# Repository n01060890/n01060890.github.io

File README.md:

# Smart Hive

Our project allows beekeepers to monitor multiple geographically distant hives via smartphones and tablets.

Externally, the Smart Hive documents changes in the hive's weight, and counts incoming and outgoing bees.
Internally, it captures multiple temperature and humidity data, in order to locate the bee cluster over the winter.

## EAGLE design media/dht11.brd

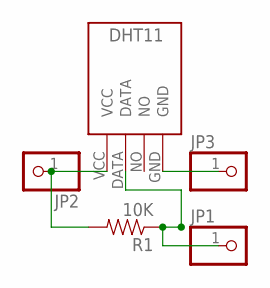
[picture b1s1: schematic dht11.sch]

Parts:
JP1, JP2, JP3: PINHD-1X1; 1X01
R1: 10K; AXIAL-0.3
U$1: DHT11

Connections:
unnamed: JP3.1, U$1.GND
unnamed: JP2.1, R1.P$2 (2), U$1.VCC
unnamed: JP1.1, R1.P$1 (1), U$1.DATA

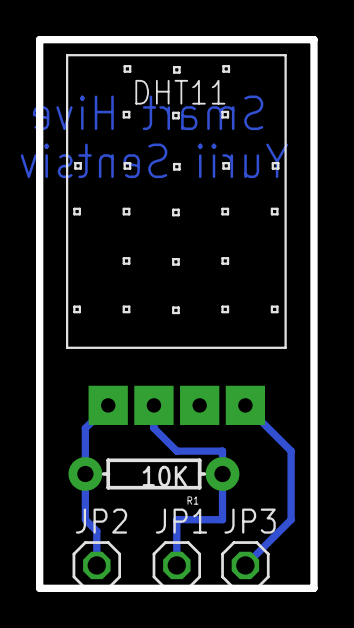
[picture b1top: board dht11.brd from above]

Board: 2 copper layers, 15.2 x 30.5 mm, 5 parts (0 on the bottom side), 3 nets.

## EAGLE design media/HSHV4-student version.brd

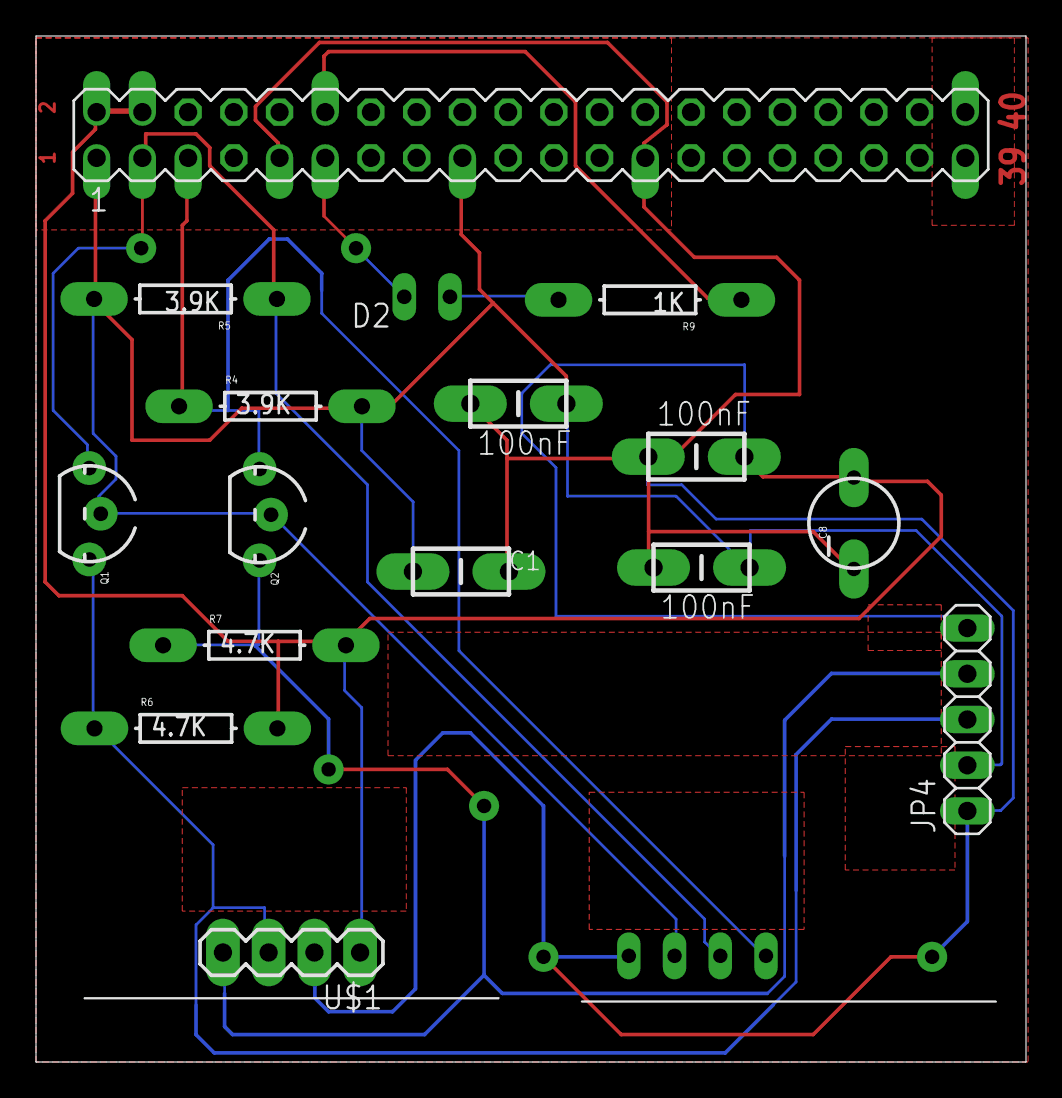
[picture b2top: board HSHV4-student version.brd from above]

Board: 2 copper layers, 55.0 x 57.0 mm, 17 parts (0 on the bottom side), 10 nets.

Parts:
C1, C2, C4, C5: 100nF; CAP-PTH-SMALL-KIT
C8: 10uF; CPOL-RADIAL-10UF-25V
D2: LED3MM-NS
IC1: DS3231; 8PTH
JP4: 1X05
K1: PIN20X2; PIN_20X2
Q1, Q2: MOSFET-NCHANNEL2N7000; TO-92
R4, R5: 3.9K; AXIAL-0.3
R6, R7: 4.7K; AXIAL-0.3
R9: 1K; AXIAL-0.3
U$1: PCF8591; 1X04

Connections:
+3V3: C1.1, C2.1, C4.2, IC1.2, JP4.2, K1.1, K1.17, Q1.2, Q2.2, R4.P$2, R5.P$2
+5V: C5.2, C8.1, JP4.5, K1.2, K1.4, R6.P$2, R7.P$2, U$1.1
GND: C1.2, C2.2, C4.1, C5.1, C8.2, IC1.1, JP4.1, K1.9, K1.25, U$1.2
GPIO17: D2.K, K1.11
GPIO18: K1.12, R9.P$1
unnamed: D2.A, R9.P$2
SCL1-3: IC1.4, K1.5, Q2.1, R4.P$1
SCL1-5: JP4.4, Q2.3, R7.P$1, U$1.4
SDA1-3: IC1.3, K1.3, Q1.1, R5.P$1
SDA1-5: JP4.3, Q1.3, R6.P$1, U$1.3

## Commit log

2016-09-20 Set up
2016-09-20 Updating content
2016-09-20 Picture resize
2016-09-20 Picture fix
2016-09-20 image resizing
2016-10-04 Updating web page
    Updating the progress
2016-10-04 Menu update
    Updating the navigation
2016-10-11 Week 6 update
2016-10-11 Week 6
    picture update
2016-10-11 Week 6
    Update
2016-10-25 Week 7
    Added week 7 content
2016-10-25 Week 8
    Added week 8 content
2016-10-25 Week 8(resubmission)
    Content is not visible
2016-10-25 Week 8(update)
    Placard link added
2016-10-25 Week 8(update)
    content not showing
2016-11-01 Week 9
    Adding content
2016-11-01 Week 9(added)
    Content not showing. Resubmission
2016-11-08 Week 10
    Progress report
2016-11-08 Week 10
    Content invisible
2016-11-15 Update directory
    Managing files folders
2016-11-15 Adding code
    Current code that I've used to get readings and display them into graph.
2016-11-15 Week 11
    Updating report
2016-11-22 Week 12
    Added progress perort on Week 12
2016-11-22 Week 12(content fix)
    Content is not appearing on web page.
2016-11-22 Week 12(fix)
2016-11-29 Week 13
    Presentation
2016-11-29 week 13
    adding media
2016-11-29 week 13
    fix
2016-12-06 Week 14
    Adding content
2016-12-06 Week 14
    Content fix
2016-12-06 Build Log
    Added Build Log page
2016-12-06 Build Log (fix)
2016-12-06 Build Log(Fix)
    Fixing html code, by replacing the C tags
2016-12-06 Build Log(fix 3)
    Updated buildlog page
2016-12-06 Build Log(fix 5)
    main page link
2016-12-11 Build Log(fix 6)
    added link to Build log in desription
2016-12-11 Build Log(Full update)
    Full update, with all files
2016-12-11 Build Log(Link fix)
    Deleted link to word file.
2016-12-13 Week 15
    30 sec video script
2017-03-09 Updated code for Integration
    IO pins are changed for readings, as was previously discussed.
2017-03-09 IO pins fix
2017-03-14 Pins Updated
2017-04-07 Picture size changed

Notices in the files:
parts and their libraries:
SparkFun-Resistors: Licensing: Creative Commons ShareAlike 4.0 International - https://creativecommons.org/licenses/by-sa/4.0
